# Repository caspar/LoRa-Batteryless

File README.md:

data dashboard website for LoRa sensor

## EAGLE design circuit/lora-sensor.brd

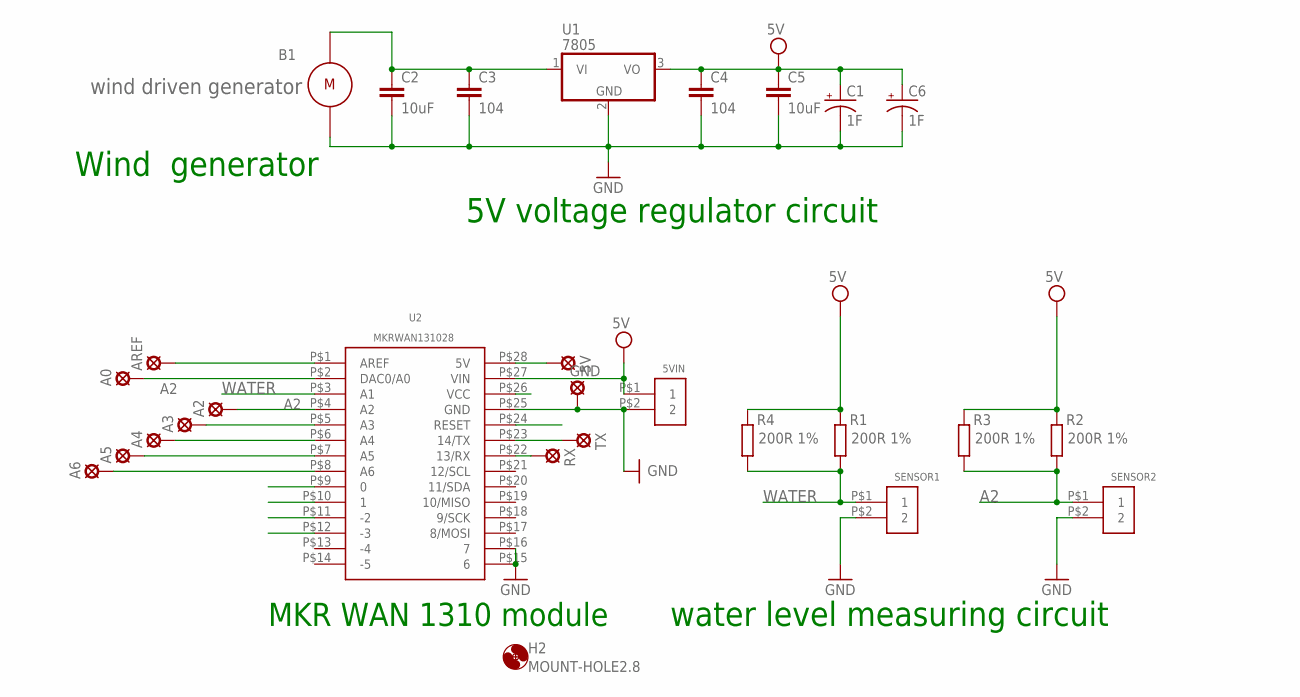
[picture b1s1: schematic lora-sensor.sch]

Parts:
5V: SE14
5VIN: 0-190ΩCON2; CON-2
A0, A2, A3, A4, A5, A6: SE14
AREF: SE14
B1: wind driven generator; MOTOR
C1, C6: 1F; E3,5-8
C2, C5: 10uF; C025-030X050
C3, C4: 104; C025-030X050
GND: SE14
H2: MOUNT-HOLE2.8; 2,8
R1, R2, R3, R4: 200R 1%; 0309/12
RX: SE14
SENSOR1, SENSOR2: 0-190ΩCON2; CON-2
TX: SE14
U1: 7805; TO220V
U2: MKRWAN131028; 28

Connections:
5V: 5VIN.P$1 (1), C1.+, C4.1, C5.1, C6.+, U1.3 (VO), U2.P$27 (VIN)
A2: A2.MP, R2.2, R3.2, SENSOR2.P$1 (1), U2.P$4 (A2)
GND: 5VIN.P$2 (2), B1.P$2, C1.-, C2.2, C3.2, C4.2, C5.2, C6.-, GND.MP, SENSOR1.P$2 (2), SENSOR2.P$2 (2), U1.2 (GND), U2.P$15 (6), U2.P$16 (7), U2.P$25 (GND)
unnamed: B1.P$1, C2.1, C3.1, U1.1 (VI)
unnamed: A3.MP, U2.P$5 (A3)
unnamed: A4.MP, U2.P$6 (A4)
unnamed: A5.MP, U2.P$7 (A5)
unnamed: A6.MP, U2.P$8 (A6)
unnamed: A0.MP, U2.P$2 (DAC0/A0)
unnamed: AREF.MP, U2.P$1 (AREF)
unnamed: 5V.MP, U2.P$28 (5V)
unnamed: TX.MP, U2.P$23 (14/TX)
unnamed: RX.MP, U2.P$22 (13/RX)
WATER: R1.2, R2.1, R3.1, R4.2, SENSOR1.P$1 (1), U2.P$3 (A1)
WATER1: R1.1, R4.1

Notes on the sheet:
Wind generator
MKR WAN 1310 module
water level measuring circuit
5V voltage regulator circuit

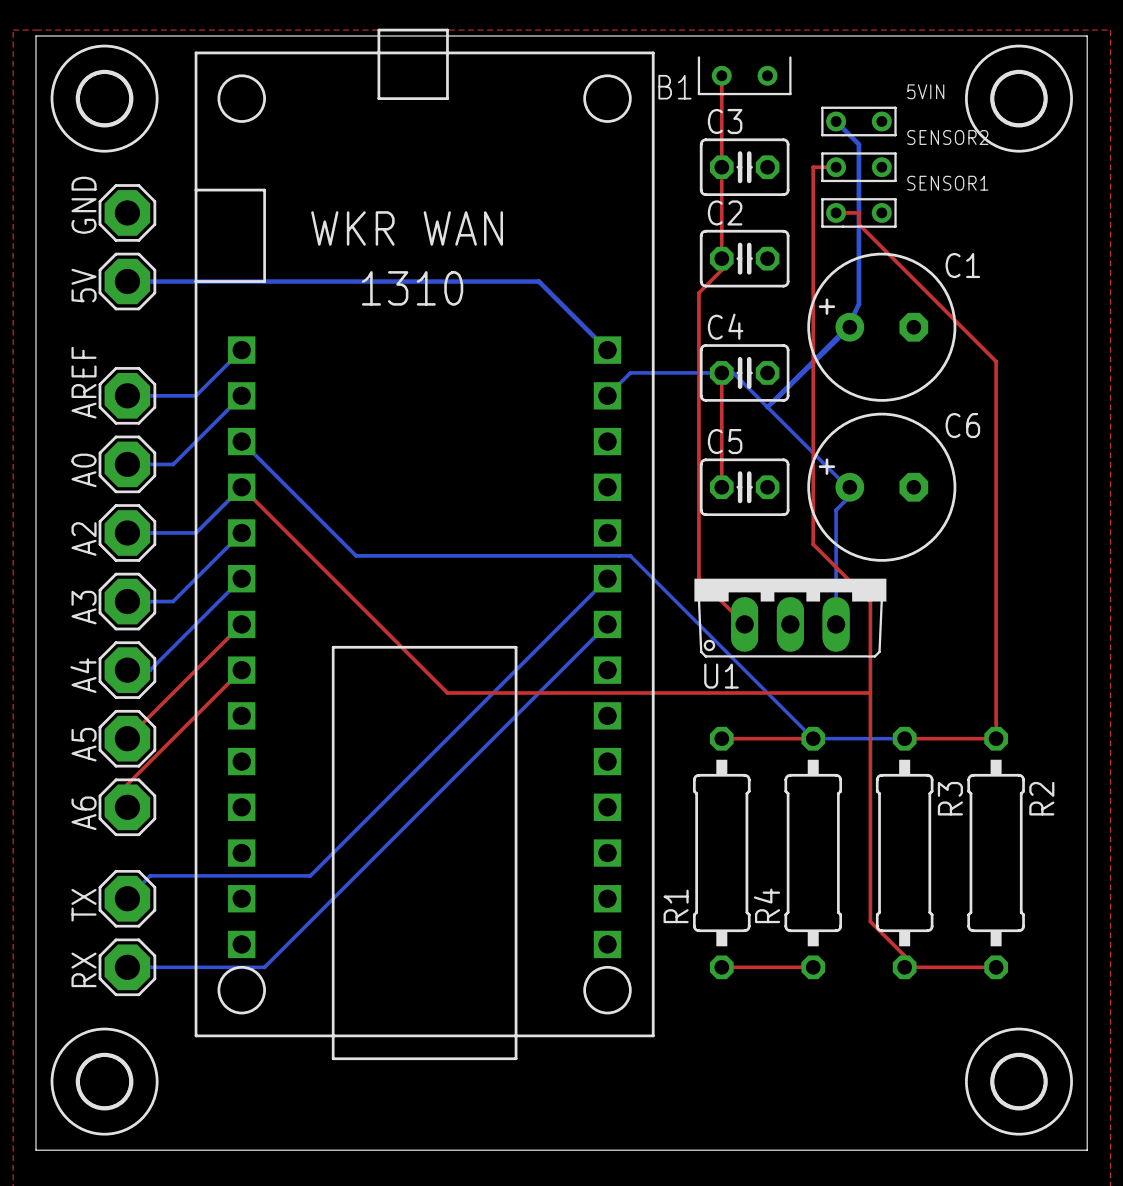
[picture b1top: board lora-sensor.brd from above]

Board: 2 copper layers, 58.4 x 61.9 mm, 31 parts (0 on the bottom side), 15 nets.

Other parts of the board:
H1, H9, H10: MOUNT-HOLE2.8; 2,8

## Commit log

2023-06-04 LoRaWAN communication without water measuring
2023-06-21 Temperature Humidity
2023-06-21 communication with TTN
2023-08-31 vercel config
2023-08-31 add site/
2023-08-31 dirs
2023-08-31 config
2023-08-31 vercel.json
2023-08-31 move templates/ directory
2023-08-31 restructure dirs
2023-08-31 sitll broken...
2023-08-31 now please please pleasE
2023-08-31 ok now it has to work
2023-08-31 css styling
2023-08-31 javascript
2023-10-13 RC Calculator Scripts
    Added scripts for estimating required capacitance per limited impulse and vice versa. LTSpice circuit simulation.
2023-12-11 AB01 Initial Power Profiling
2023-12-12 PPK2 Analysis + Viz
2023-12-16 remove large file— it will go in the google drive data directory. you can access it programatically in python
2024-04-19 Data + viz
2024-06-28 Optimization fixes
2024-07-01 More optimization bug fixes
2024-07-01 Residual Plotting
2024-07-08 Avg power calculations
2024-07-08 Uncertainty bars
2024-07-08 Moved clustering to viz file
2024-07-08 Model results plot fix
2024-07-08 Plot fix
